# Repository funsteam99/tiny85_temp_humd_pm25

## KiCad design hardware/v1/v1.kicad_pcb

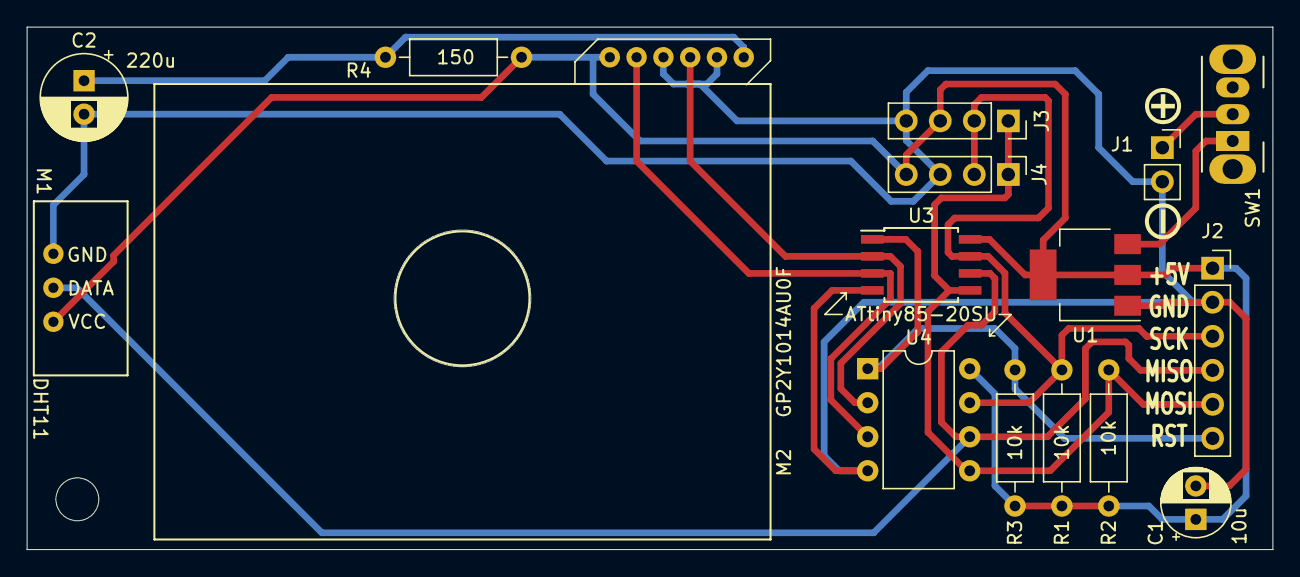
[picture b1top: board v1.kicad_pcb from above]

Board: 2 copper layers, 93.0 x 39.0 mm, 17 parts (0 on the bottom side), 11 nets.

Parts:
C1: 10u; CP_Radial_D5.0mm_P2.50mm
C2: 220u; CP_Radial_D6.3mm_P2.50mm
H1: MountingHole; MountingHole_3.2mm_M3
J1: 9V_in; PinSocket_1x02_P2.54mm_Vertical
J2: To_Programmer; PinSocket_1x06_P2.54mm_Vertical
J3: SSD1306; PinSocket_1x04_P2.54mm_Vertical
J4: SSD1306; PinHeader_1x04_P2.54mm_Vertical
M1: DHT11
M2: GP2Y1014AU0F
R1, R2, R3: 10k; R_Axial_DIN0207_L6.3mm_D2.5mm_P10.16mm_Horizontal
R4: 150; R_Axial_DIN0207_L6.3mm_D2.5mm_P10.16mm_Horizontal
SW1: SW_SPST; SW_CuK_OS102011MA1QN1_SPDT_Angled
U1: LT1117-5.0; SOT-223-3_TabPin2
U3: ATtiny85-20SU; SOIJ-8_5.3x5.3mm_P1.27mm
U4: ATtiny85-20PU; DIP-8_W7.62mm

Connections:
+5V: C1.1, J2.1, J3.3, J4.4, M1.1, M2.6, R1.1, R2.1, R3.1, R4.2, U1.2, U3.8, U4.8
/MISO: J2.4, M1.2, U3.6, U4.6
/PB3: M2.3, U3.2, U4.2
/PB4: M2.5, U3.3, U4.3
/RST: J2.6, R3.2, U3.1, U4.1
/SCL: J2.3, J3.2, J4.2, R1.2, U3.7, U4.7
/SDA: J2.5, J3.1, J4.1, R2.2, U3.5, U4.5
GND: C1.2, C2.2, J1.2, J2.2, J3.4, J4.3, M1.3, M2.2, M2.4, U1.1, U3.4, U4.4
unnamed: C2.1, M2.1, R4.1
unnamed: J1.1, SW1.2
unnamed: SW1.1, U1.3
